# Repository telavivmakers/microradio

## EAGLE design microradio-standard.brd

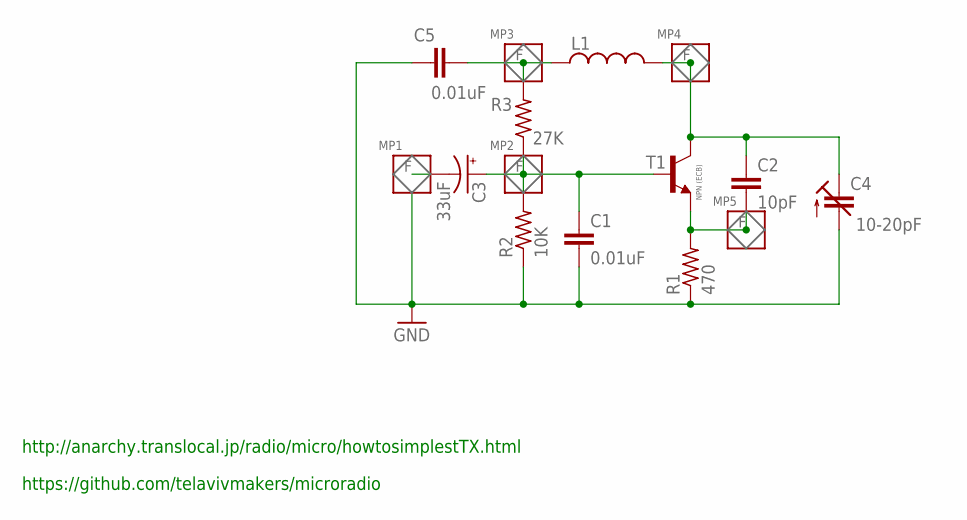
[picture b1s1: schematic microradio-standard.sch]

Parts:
C1, C5: 0.01uF; M1206
C2: 10pF; C5B3
C3: 33uF; 153CLV-0405
C4: 10-20pF; 3008
L1: L-US0204/5; 0204/5
MP1, MP2, MP3, MP4, MP5: MICROSTRIPMI; MICROSTRIP_5X5MM
R1: 470; R1206
R2: 10K; R1206
R3: 27K; R1206
T1: NPN (ECB); TO92-BCE

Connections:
GND: C1.2, C4.- (A), C5.2, R1.1, R2.1
unnamed: C3.-, MP1.F
unnamed: C2.2, MP5.F, R1.2, T1.E
unnamed: C5.1, L1.1, MP3.F, R3.2
unnamed: C1.1, C3.+, MP2.F, R2.2, R3.1, T1.B
unnamed: C2.1, C4.+ (E), L1.2, MP4.F, T1.C

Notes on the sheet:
http://anarchy.translocal.jp/radio/micro/howtosimplestTX.html
https://github.com/telavivmakers/microradio

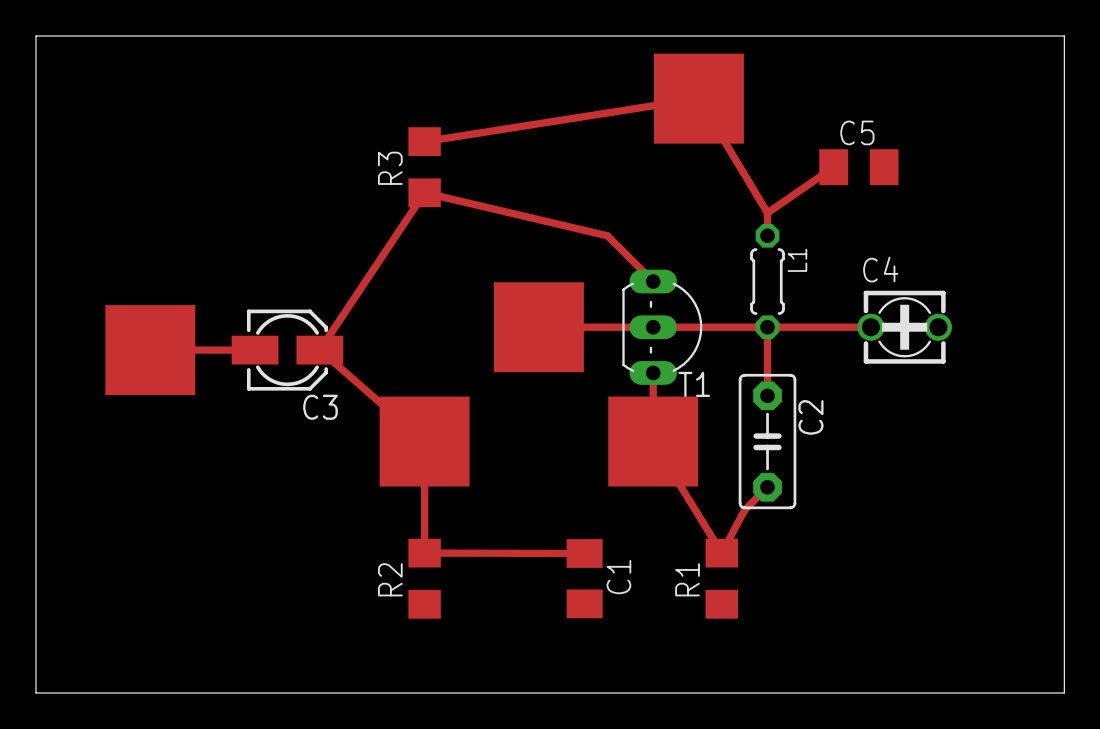
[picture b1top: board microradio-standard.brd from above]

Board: 2 copper layers, 57.1 x 36.5 mm, 15 parts (0 on the bottom side), 6 nets.

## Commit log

2017-02-17 pcb version
2017-02-17 added lib
2017-02-17 moving to smd
2017-02-17 smd version, is this legfit microstrip?
